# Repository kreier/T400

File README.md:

# T400

Robot car with WiFi, programmed and controlled by MicroPython. The OLED screen gives information about status, connection and WiFi network to connect to (AP mode).

## Project

This car was build during ASA session III in 2019/2020 at the AISVN. In 11 weeks from February 24th to May 22nd we successfully created 8 robot cars. Here are some pictures of the finished products:

### Key features

Over the time of 3 months the students will reach different stages of their project, but here are some key features:

- Central unit is a ESP8266 with 32 kByte RAM and 4 GByte Flash memory, running at 160 MHz.
- The programming language is [MicroPython](https://en.wikipedia.org/wiki/MicroPython) with an interactive prompt [REPL](https://en.wikipedia.org/wiki/Read%E2%80%93eval%E2%80%93print_loop).
- The control unit is powered by a standard 5V powerbank.
- The drive unit is a caterpillar base with two 12V motors.
- The robot car can be controlled via WiFi.
- An OLED display 128x64 (ssd1306) gives status updates.

## Materials

The materials used for this project were ordered at [IC ĐÂY RỒI](https://icdayroi.com/), [thegioiic.com](https://thegioiic.com/) and [lazada.vn](https://www.lazada.vn/#). Here is a list of materials:

| Nr | Name        | Amount | Unit Price |   Sum   |    Supplier    |
|:--:|-------------|:------:|-----------:|--------:|:--------------:|
|  1 |ESP8266 NodeMCU | 1     | 83000 VND| 83000 VND| [link thegioiic](https://thegioiic.com/products/lua-esp8266-cp2102-nodemcu-wifi-module) |
| 2 |Motor Shield L293D | 1 | 30000 VND| 30000 VND| [link thegioiic](https://thegioiic.com/products/esp12e-lua-l293d-de-ra-chan-wifi-esp8266-nodemcu) |
| 3 |OLED display 126x64 I2C | 1 | 79000 VND| 79000 VND| [link thegioiic](https://thegioiic.com/products/lcd-oled-0-96inch-128x64-iic-4pin-chu-trang) |
| 4 |Wires DuPont MF and FF | 20 |   300 VND| 6000 VND| [link thegioiic](https://thegioiic.com/products/day-be-cai-cai-dai-15cm) |
| 5 |Robot caterpillar 12V unit | 1 | 483000 VND| 483000 VND| [link lazada.vn](https://www.lazada.vn/products/smart-tank-car-chassis-tracked-caterpillar-crawler-robot-platform-with-dual-dc-12v-motor-for-diy-for-arduino-t101-ptp101-i402162026-s693860633.html?spm=a2o4n.searchlist.list.162.24b0381feoC1Mg&search=1) |
| 6 |Powerbank 10000 mAh 2 USB | 1 | 249000 VND| 249000 VND| [link nguyenkim](https://www.nguyenkim.com/pin-sac-du-phong-mili-power-shine-ii-hb-m90bk.html) |
| 7 |DC step-up converter 5V 12V | 1 | 23000 VND| 23000 VND| [link thegioiic](https://thegioiic.com/products/xl6009-mach-tang-ap-4a) |
| 8 |Robot 4DOF kit | 1 | 246000 VND| 246000 VND| [link lazada.vn](https://www.lazada.vn/products/4-dof-acrylic-chua-lap-rap-diy-canh-tay-robot-diy-bo-cho-arduino-may-lam-ho-tro-hoc-tap-sg90-servo-i267650656-s391094259.html) |
| 9 |Servo SG90 | 5 | 29000 VND| 145000 VND| [link icdayroi](https://icdayroi.com/servo-sg90) |
| 10 |Ultrasonic Module US-100 3.3V | 1 | 59000 VND| 59000 VND| [link thegioiic](https://thegioiic.com/products/us-100-module-cam-bien-sieu-am) |
| 11 |I2C servo controller PCA9685 | 1 | 49000 VND| 49000 VND| [link thegioiic](https://thegioiic.com/products/pca9685-dieu-khien-dong-co-servo-12bit-pwm-6-kenh) |
| 12 |USB male connector Type A | 2 | 1800 VND| 3600 VND| [link thegioiic](https://thegioiic.com/products/cong-usb2-0-typea-4pin-dau-duc-han-day) |
| 13 |Buzzer 3.3 Volt | 1 | 3000 VND| 3000 VND| [link thegioiic](https://thegioiic.com/products/module-coi-buzzer-3-3v-5v) |
| 14 |Screw M3 8mm | 8 | 550 VND| 4400 VND| [link thegioiic](https://thegioiic.com/products/vit-pm-m3-x-8mm) |
| 15 |HEX-M3 spacer 15mm | 4 | 1000 VND| 4000 VND| [link thegioiic](https://thegioiic.com/products/tru-dong-hex-m3-cai-cai-dai-15mm) |
|  | |  |  VND| 1467000 VND|  |

## Pin layout

## Code

This is an example of the MicroPython code we are going to use:

``` py
from machine import Pin, I2C
import ssd1306

# ESP32 Pin assignment 
# i2c = I2C(1, scl=Pin(22), sda=Pin(21))

# ESP8266 Pin assignment
i2c = I2C(scl=Pin(12), sda=Pin(14))

oled_width = 128
oled_height = 64
oled = ssd1306.SSD1306_I2C(oled_width, oled_height, i2c)

# draw some boxes

for x in range(0, 127): # horizontal lines
  oled.pixel(x, 0, 1)
  oled.pixel(x, 15, 1)
  oled.pixel(x, 16, 1)
  oled.pixel(x, 63, 1)
  
for y in range(0, 63): # vertical lines
  oled.pixel(0, y, 1)
  oled.pixel(127, y, 1)

oled.text('T400 Robot Car', 8, 4)
oled.text('Programmed in', 4, 22)
oled.text('MicroPython on', 4, 32)
oled.text('a ESP8266.', 4, 42)
oled.text('Used at AISVN.', 4, 52)
  
oled.show()
```

## I2C connector

`2020/07/09`

Following the inspiration of SparkFun with their [QWIIC](https://www.sparkfun.com/qwiic#products) connector I tried to replicate the pin order. But instead of SMD 1.0 mm connector I just use the regular 2.54mm raster with XH connector on the board and respective 4 pin connector wire.

Following the same order the pins are assigned:
1. black - GND
2. red - 3.3 V
3. blue - SDA
4. yellow - SCL

The order does not match several OLED displays, but the ZS-042 rtc clock, the 1602 display adapter and many more.

`2020/11/27`

With the new [T-Display](https://kreier.github.io/t-display/) project I included the I2C connector as well. The pins look like this:

At the ESP32 SCL (SCK) is on GPIO 22 and SDA (SDI) is on GPIO 21.

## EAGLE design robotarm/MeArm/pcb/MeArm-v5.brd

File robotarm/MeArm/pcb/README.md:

# PCB for MeArm3

The MeArm 3.0 uses a custom PCB to connect the 4 servos to a single flat cable with 6 pins and provide a physical base plate for the ground servo at the same time.

From the assemble video you can guess the shape:

Since the shematics is not provided, it has to be recreated in EAGLE. Here my attempts: 

The files are located in this folder and sourced from [here](https://www.thingiverse.com/thing:3420797/files) and [here](https://github.com/mimeindustries/MeArm). The modification is the removal of the text for the lasercutting and shortend of some corners to fit on the base of the robot.

## PCB

The files for the PCB are not provided, so they have to be recreated. This file should serve as inspiration, the rations are all given in the dxf file or can be measured there:

## Additional materials

Aside from the laser cut 3mm acrylic we need some M2.5 screws, no nuts! That's said [here in the video](https://youtu.be/sPdbs9b5udQ?t=455). So I count:

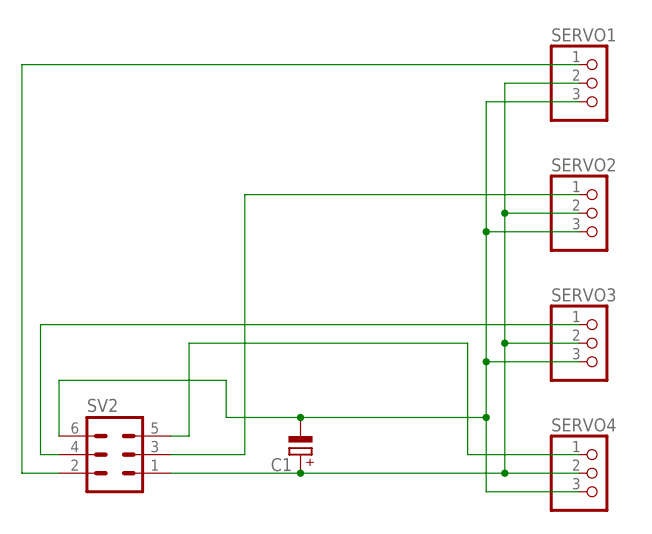
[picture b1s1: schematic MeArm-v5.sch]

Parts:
C1: CPOL-EUE2.5-6; E2,5-6
SERVO1, SERVO2, SERVO3, SERVO4: PINHD-1X3; 1X03
SV2: ML6

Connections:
unnamed: C1.+, SERVO1.2, SERVO2.2, SERVO3.2, SERVO4.2, SV2.1
unnamed: SERVO4.1, SV2.5
unnamed: SERVO2.1, SV2.3
unnamed: SERVO1.1, SV2.2
unnamed: C1.-, SERVO1.3, SERVO2.3, SERVO3.3, SERVO4.3, SV2.6
unnamed: SERVO3.1, SV2.4

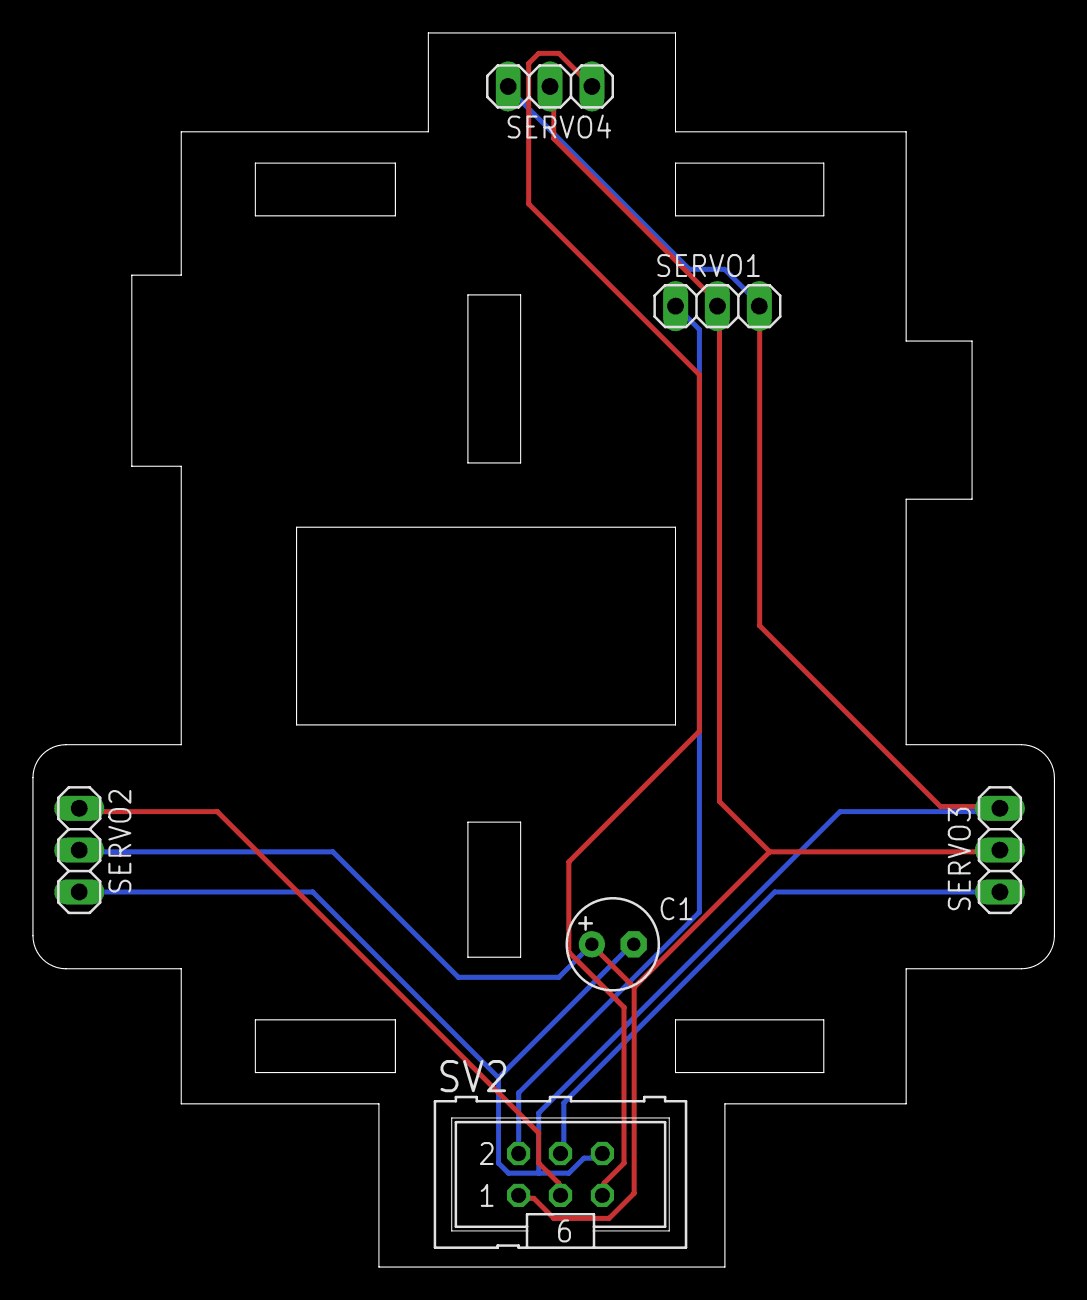
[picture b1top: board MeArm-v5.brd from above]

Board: 2 copper layers, 62.0 x 74.9 mm, 6 parts (0 on the bottom side), 6 nets.

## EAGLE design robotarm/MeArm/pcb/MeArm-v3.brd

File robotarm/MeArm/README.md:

# Robot arm at T400

Limited time and resources led to the decision to use the MeArm v3.0 for our T400 project during ASA3. The assembly should take 25 minutes and can be followed [in this video](https://youtu.be/sPdbs9b5udQ).

The files are located in this folder and sourced from [here](https://www.thingiverse.com/thing:3420797/files) and [here](https://github.com/mimeindustries/MeArm). The modification is the removal of the text for the lasercutting and shortend of some corners to fit on the base of the robot.

## PCB

The files for the PCB are not provided, so they have to be recreated. This file should serve as inspiration, the rations are all given in the dxf file or can be measured there:

## Additional materials

Aside from the laser cut 3mm acrylic we need some M2.5 screws, no nuts! That's said [here in the video](https://youtu.be/sPdbs9b5udQ?t=455). So I count:

- 16x - M2.5 x 6mm
- 18x - M2.5 x 10mm
- 2x  - M2.5 x 16mm

I'll give it a try on January 31st, 2020.

## Licence

User phenoptix (Ben Gray from Nottingham) from Mime industries/MeArm published the following information on his website regarding the licence:

The hardware is released under [Creative Commons Share-alike 3.0](https://creativecommons.org/licenses/by-sa/3.0/).

All other code is open source so please feel free to do anything you want with it; you buy me a beer if you use this and we meet someday (Beerware license). Also this boiler plate is yoinked from Sparkfun with thanks. Images are CC-SA-NC soz, have the files and design but take your own pics ;)

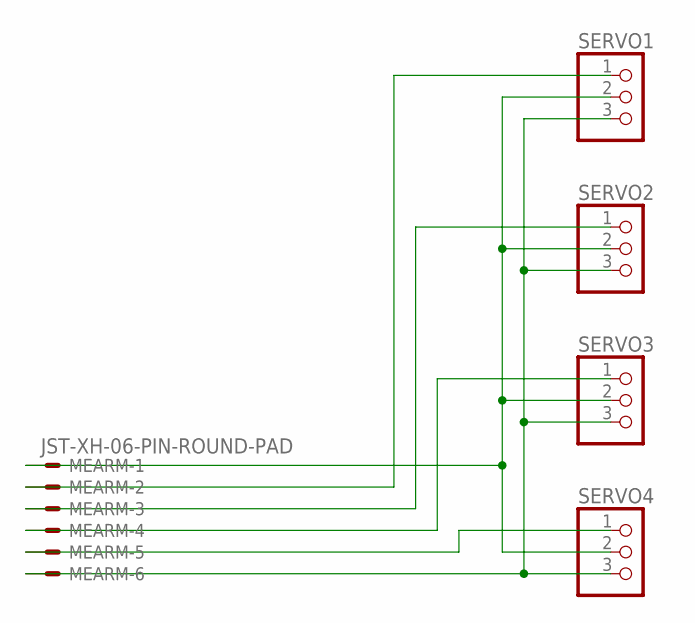
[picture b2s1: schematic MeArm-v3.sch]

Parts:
MEARM: JST-XH-06-PIN-ROUND-PAD; JST-XH-06-PACKAGE-ROUND-PAD
SERVO1, SERVO2, SERVO3, SERVO4: PINHD-1X3; 1X03

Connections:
unnamed: MEARM.1, SERVO1.2, SERVO2.2, SERVO3.2, SERVO4.2
unnamed: MEARM.5, SERVO4.1
unnamed: MEARM.4, SERVO3.1
unnamed: MEARM.2, SERVO1.1
unnamed: MEARM.3, SERVO2.1
unnamed: MEARM.6, SERVO1.3, SERVO2.3, SERVO3.3, SERVO4.3

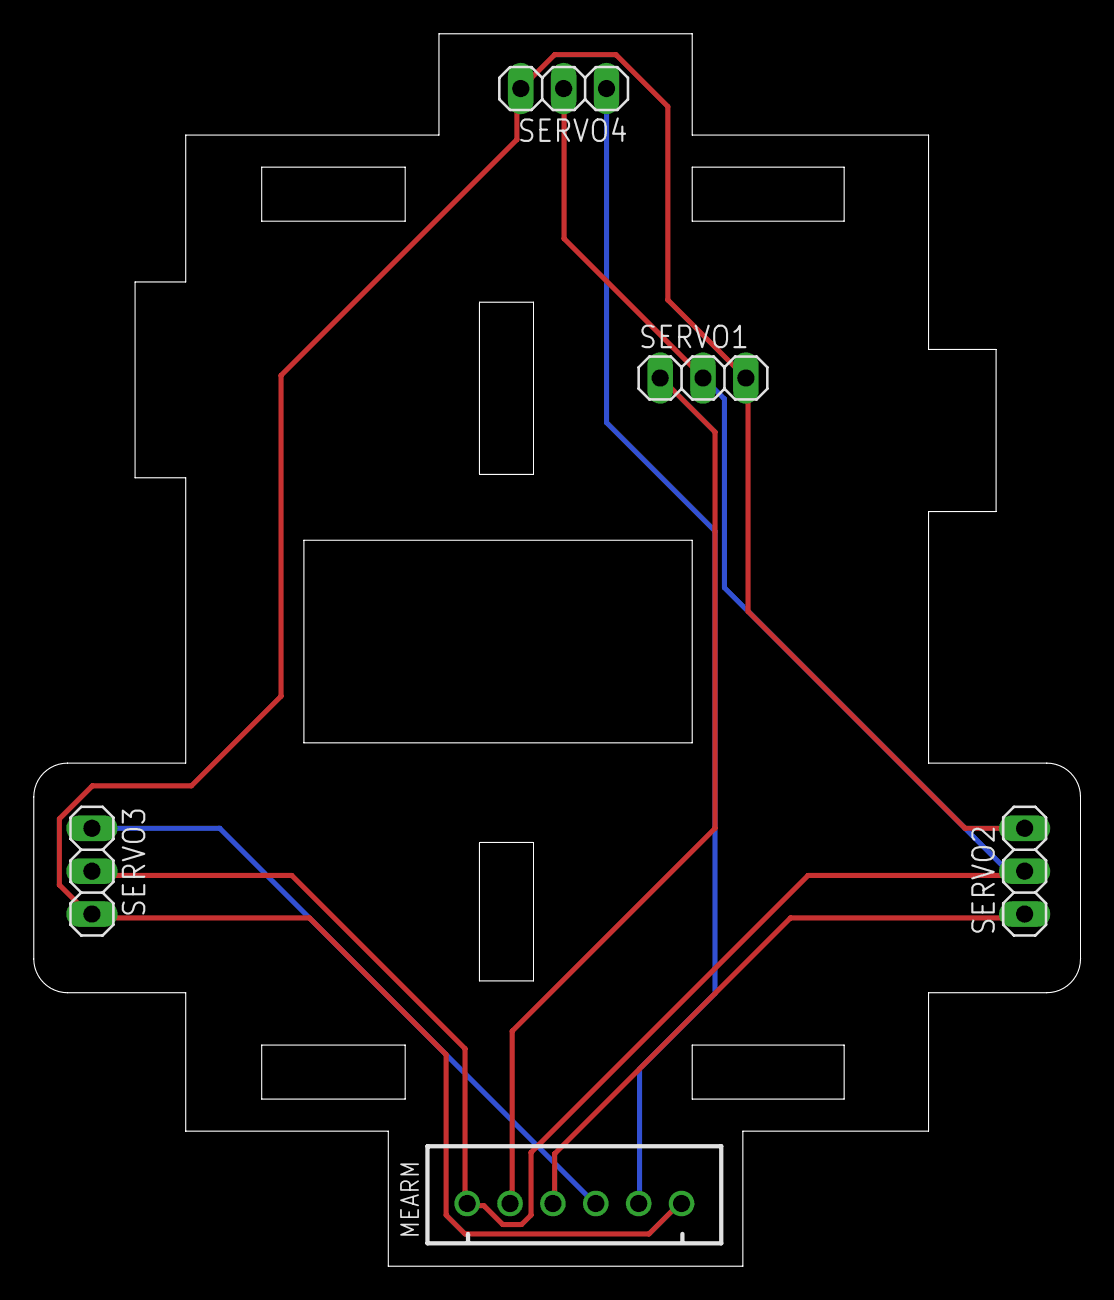
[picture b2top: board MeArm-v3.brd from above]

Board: 2 copper layers, 62.0 x 73.0 mm, 5 parts (0 on the bottom side), 6 nets.

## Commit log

2019-12-05 2019-12-05
2019-12-11 pin assignment
2019-12-11 2019/12/10
2019-12-11 code with reassigned i2c
2019-12-11 simpler
2019-12-11 2019/12/12 saved 5 lines
2019-12-11 from DOIT Shanghai
2019-12-16 SDA D6 and SCL D5 updated
2019-12-16 code from Vincent Lacour
2019-12-19 Update LICENSE
2019-12-19 example to activate travis
2019-12-19 included requirements.txt
2019-12-19 added Micropython-machine
2019-12-19 Micropython is based on python 3.4
2019-12-19 micropython?
2019-12-19 badge for license
2019-12-19 it's so simple
2019-12-19 calculate the prime numbers until 1000
2019-12-19 for now only python since machine can't be imported
2019-12-23 reorganized 2019/12/23
2019-12-23 sort python and micropython
2019-12-23 check python3
2019-12-23 remove codecov, check at least 3 progams
2019-12-23 welcome OLED message
2019-12-23 sample photos
2019-12-23 reorganized pictures
2019-12-23 included pictures
2019-12-23 image 2019/12/23
2019-12-23 Set theme jekyll-theme-cayman
2019-12-23 custom title
2019-12-23 different colors
2019-12-23 relocated
2019-12-25 build 2019/12/23
2019-12-25 created 2019/12/23 and programmed with MicroPython
2019-12-25 updated image from T400 lite
2019-12-26 list of materials and code included
2019-12-26 slimmed down table for webpage
2019-12-26 minor typos
2019-12-27 converted to blue style
2019-12-30 updated materials list
2019-12-30 removed old list
2020-01-08 assigned pins
2020-01-08 code and pin update
2020-01-08 oled reorganized
2020-01-08 converted image 2020/01/08
2020-01-08 lastest splash screen with running clock
2020-01-13 method .frambuf not needed with new library
2020-01-13 extended robotarm
2020-01-13 more pictures for differen robot arms
2020-01-14 boot to webserver with oled info
2020-01-16 updated pin assignment
2020-01-23 fills screen with random pixels
2020-01-23 some noise every 200 ms
2020-01-24 clean up
2020-01-24 pictures reorganized
2020-01-27 reorganized 2020/01/27
2020-01-28 ignore Synology Diskstation
2020-01-29 upload pictures and dxf
2020-01-29 integraded MeArm 1.1 and 3.0
2020-01-29 screws included and video updated
2020-01-31 information to oled display
2020-02-10 design update
2020-02-10 Affinity Designer sketch
2020-02-10 lasercut platform v0.1 2020-02-10
2020-02-25 shape pcb pla
2020-02-26 reorganized 2020/02/27
2020-02-26 v3 dimensions fit 3d print
2020-02-28 PCB in Eagle created
2020-02-28 gerber files v1
2020-02-28 gerber detail files
2020-02-28 order at JLCPCB
2020-02-28 added capacitor, connector IDC 6P ML
2020-02-28 screenshot Fusion 360
2020-02-28 images of PCB included
2020-03-04 refined design v2
2020-07-09 included i2c connector assignment
2020-07-09 system from SparkFun
2020-07-09 xh254 replacement
2020-11-27 images relocated
2020-11-27 updated website documentation
2020-11-27 layout fix 2020/11/27
2020-11-27 updated I2C connector definition
2020-12-11 i2c connector
2022-04-22 remove hitcounter
2025-09-06 updated badges to 2025
2025-09-08 Updated T400_OLED.ino with u8g2 OLED driver
2025-09-08 new page build process

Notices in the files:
README.md:
MIT license
